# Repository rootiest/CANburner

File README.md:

# CANBurner

This Project originated from the idea of making the swapping process of the Stealthburner front easier.

CANBurner is a PCB design, that works in cooperation with Hartk's 2pc PCB design.

It consists of a front-part and our adapted CANBurner
The CANBurner is the connection PCB between an EBB36 or EBB42 or any CAN module and the movable front PCB.
over the course of the revisions functions were added and the design was changed. 

# Changelog:
## Rev 1.0 (initial design; tested) 19.10.2022

- adapted the footprint of Hartk's Backplate to fit for our purpose
- JST-XH connectors for 2x fans (Hotend and Part-cooling) and 1x LED added
- 2x3 angled pin header to connect to the front PCB 
- simple wire paths over the board
- a through-hole design for easy soldering at home

first tests by André show, that the design fits perfectly on the CW2 extruder. dimensions reach barely past the motor backplate. 
THD components don't collide with each other or the SB. Functions are fully present and the JST connectors make swapping cables easy.
Space can be used more effectively. JST is not as important, the cables can be soldered directly on the Board.

## Rev 2.0 04.11.2022

- Name CANBurner was suggested by rootiest
- added one more JST-XH for I2C connection
- added 2x4 angled pin header 
- placement of connectors were changed
- added Voron Logo 
- minor cleanup of traces and text

## Rev 2L 05.11.2022

- added Neopixel SMD light as status LED
- changed traces
- added voltage test-points for 24V, 5V and GND
- added "rootiest"-Logo

## Rev 3

- fully changed plug design
- one 8 pin JST-PH to connect to CAN board
- 4 pin socket header to allow for direct I2C connection
- SMD LED and solder traces to skip LED when its ot used

## Credits

CANBurner is a collaboration between [Chris Laprade](https://github.com/rootiest/) and [André Bernbrich](https://github.com/Peviox)

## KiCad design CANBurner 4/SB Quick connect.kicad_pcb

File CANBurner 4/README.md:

<!--
 Copyright (C) 2022 Chris Laprade (chris@rootiest.com)
 
 This file is part of CANburner.
 
 CANburner is free software: you can redistribute it and/or modify
 it under the terms of the GNU General Public License as published by
 the Free Software Foundation, either version 3 of the License, or
 (at your option) any later version.
 
 CANburner is distributed in the hope that it will be useful,
 but WITHOUT ANY WARRANTY; without even the implied warranty of
 MERCHANTABILITY or FITNESS FOR A PARTICULAR PURPOSE.  See the
 GNU General Public License for more details.
 
 You should have received a copy of the GNU General Public License
 along with CANburner.  If not, see <http://www.gnu.org/licenses/>.
-->

# CANBurner 3 Beta

## What is it?

CANBurner is an adaptation of hartk's 2-piece StealthBurner PCB.

CANBurner adapts this concept for use on printers with a CANbus toolhead like the BigTreeTech EBB or the Mellow FLY-SHT.

## What is new in the v3 Beta?

Version 3 introduces a new single-connector interface to the toolboard. There is also a solder-bridge for bypassing the onboard LED and a header for directly-attaching i2c devices.

## How does it work?

Just like [hartk's boards](https://github.com/hartk1213/MISC/tree/main/PCBs/Stealthburner_Toolhead_PCB) do!

[Watch this video](https://www.youtube.com/watch?v=PCIwZRPYMZ8)

Instead of attaching a ribbon, our board just connects to the corresponding pins on your CANbus toolboard.

Its purpose is to act as a "quick-connect" bridge that allows you to remove the stealthburner without disconnecting and reconnecting several connectors for components like fans and LEDs.

The pins will align and connect when you attach the stealthburner front to the extruder.

## Credits

CANBurner is a collaboration between [Chris Laprade](https://github.com/rootiest/) and [André Bernbrich](https://github.com/Peviox)

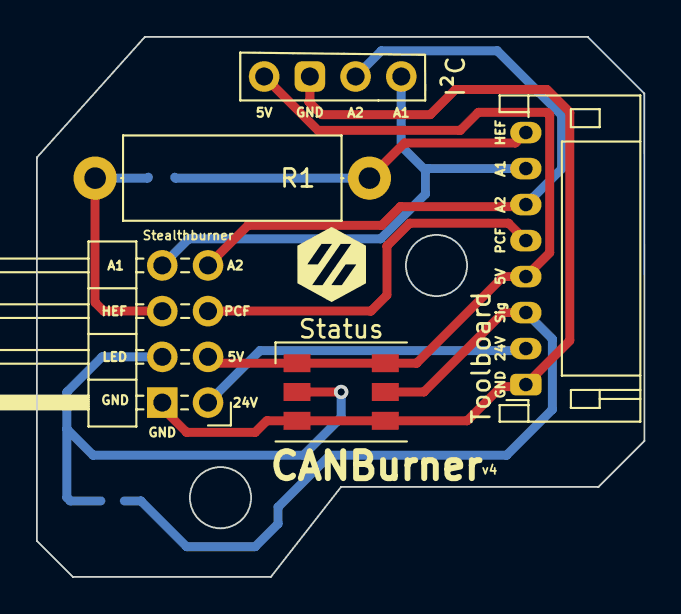
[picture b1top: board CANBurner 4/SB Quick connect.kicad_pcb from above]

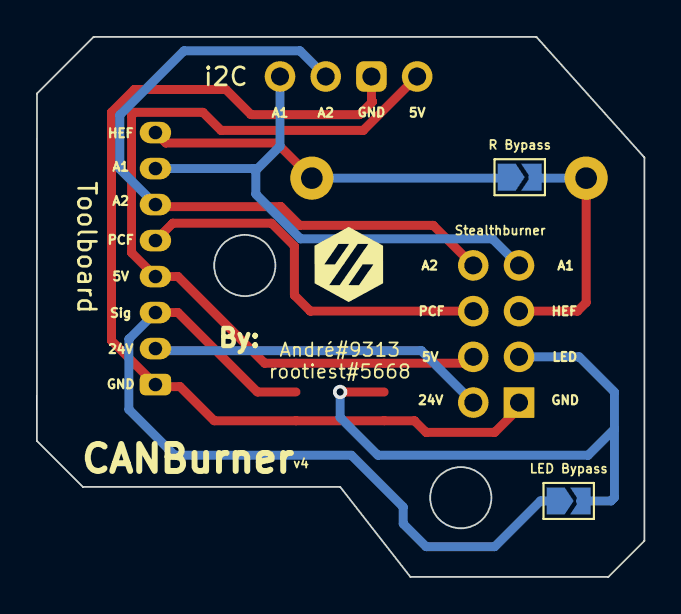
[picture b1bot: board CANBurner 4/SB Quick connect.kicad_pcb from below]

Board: 2 copper layers, 33.8 x 30.0 mm, 7 parts (2 on the bottom side), 8 nets.

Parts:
I²C: i2C Addon; PinSocket_1x04_P2.54mm_Vertical
J1: Conn_02x04_Odd_Even; PinHeader_2x04_P2.54mm_Horizontal
LED Bypass: LED Bypass; SolderJumper-2_P1.3mm_Open_TrianglePad1.0x1.5mm
R1: R; R_Axial_DIN0414_L11.9mm_D4.5mm_P15.24mm_Horizontal
R Bypass: LED Bypass; SolderJumper-2_P1.3mm_Open_TrianglePad1.0x1.5mm
Status: LED_WS2812_PLCC6_5.0x5.0mm_P1.6mm
Toolboard: JST_PH_S8B-PH-K_1x08_P2.00mm_Horizontal

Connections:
/5V: I²C.4, J1.6, Status.1, Status.6, Toolboard.4
/24V: J1.8, Toolboard.2
/A1: I²C.1, J1.1, Toolboard.7
/A2: I²C.2, J1.2, Toolboard.6
/GND: I²C.3, J1.7, Status.3, Status.4, Toolboard.1
/HEF: J1.3, R1.1, R1.2, R Bypass.1, R Bypass.2, Toolboard.8
/PCF: J1.4, Toolboard.5
/Sig: J1.5, LED Bypass.1, LED Bypass.2, Status.2, Status.5, Toolboard.3

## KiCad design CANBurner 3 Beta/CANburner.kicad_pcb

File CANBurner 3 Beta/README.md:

<!--
 Copyright (C) 2022 Chris Laprade (chris@rootiest.com)
 
 This file is part of CANburner.
 
 CANburner is free software: you can redistribute it and/or modify
 it under the terms of the GNU General Public License as published by
 the Free Software Foundation, either version 3 of the License, or
 (at your option) any later version.
 
 CANburner is distributed in the hope that it will be useful,
 but WITHOUT ANY WARRANTY; without even the implied warranty of
 MERCHANTABILITY or FITNESS FOR A PARTICULAR PURPOSE.  See the
 GNU General Public License for more details.
 
 You should have received a copy of the GNU General Public License
 along with CANburner.  If not, see <http://www.gnu.org/licenses/>.
-->

# CANBurner 3 Beta

## What is it?

CANBurner is an adaptation of hartk's 2-piece StealthBurner PCB.

CANBurner adapts this concept for use on printers with a CANbus toolhead like the BigTreeTech EBB or the Mellow FLY-SHT.

## What is new in the v3 Beta?

Version 3 introduces a new single-connector interface to the toolboard. There is also a solder-bridge for bypassing the onboard LED and a header for directly-attaching i2c devices.

## How does it work?

Just like [hartk's boards](https://github.com/hartk1213/MISC/tree/main/PCBs/Stealthburner_Toolhead_PCB) do!

[Watch this video](https://www.youtube.com/watch?v=PCIwZRPYMZ8)

Instead of attaching a ribbon, our board just connects to the corresponding pins on your CANbus toolboard.

Its purpose is to act as a "quick-connect" bridge that allows you to remove the stealthburner without disconnecting and reconnecting several connectors for components like fans and LEDs.

The pins will align and connect when you attach the stealthburner front to the extruder.

## Credits

CANBurner is a collaboration between [Chris Laprade](https://github.com/rootiest/) and [André Bernbrich](https://github.com/Peviox

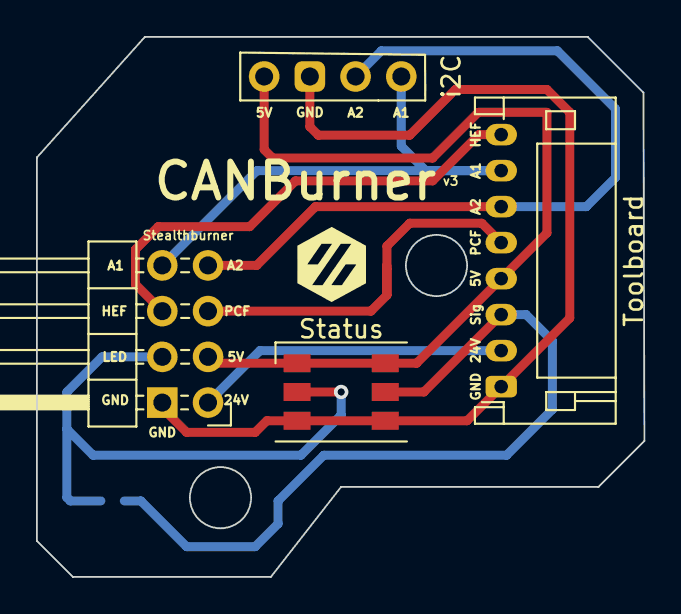
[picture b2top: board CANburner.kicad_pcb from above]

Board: 2 copper layers, 33.8 x 30.0 mm, 5 parts (1 on the bottom side), 8 nets.

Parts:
LED Bypass: LED Bypass; SolderJumper-2_P1.3mm_Open_TrianglePad1.0x1.5mm
Status: LED_WS2812_PLCC6_5.0x5.0mm_P1.6mm
Stealthburner: Conn_02x04_Odd_Even; PinHeader_2x04_P2.54mm_Horizontal
Toolboard: JST_PH_S8B-PH-K_1x08_P2.00mm_Horizontal
i2C: i2C Addon; PinSocket_1x04_P2.54mm_Vertical

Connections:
/5V: Status.1, Status.6, Stealthburner.6, Toolboard.4, i2C.4
/24V: Stealthburner.8, Toolboard.2
/A1: Stealthburner.1, Toolboard.7, i2C.1
/A2: Stealthburner.2, Toolboard.6, i2C.2
/GND: Status.3, Status.4, Stealthburner.7, Toolboard.1, i2C.3
/HEF: Stealthburner.3, Toolboard.8
/PCF: Stealthburner.4, Toolboard.5
/Sig: LED Bypass.1, LED Bypass.2, Status.2, Status.5, Stealthburner.5, Toolboard.3

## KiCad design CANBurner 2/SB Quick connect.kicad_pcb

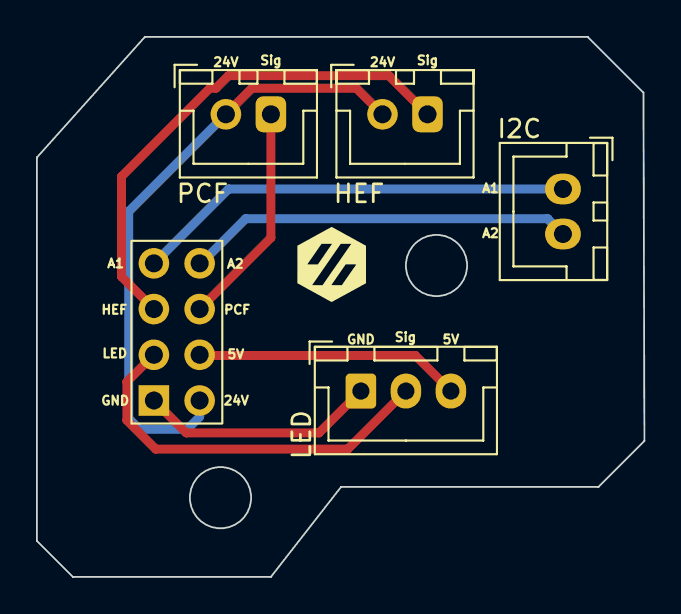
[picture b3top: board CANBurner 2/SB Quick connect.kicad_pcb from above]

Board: 2 copper layers, 33.8 x 30.0 mm, 5 parts (0 on the bottom side), 8 nets.

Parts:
HEF: Conn_01x02; JST_XH_B2B-XH-A_1x02_P2.50mm_Vertical
I2C: Conn_01x02; JST_XH_B2B-XH-A_1x02_P2.50mm_Vertical
J1: Conn_02x04_Odd_Even; PinHeader_2x04_P2.54mm_Vertical
LED: Conn_01x03; JST_XH_B3B-XH-A_1x03_P2.50mm_Vertical
PCF: Conn_01x02; JST_XH_B2B-XH-A_1x02_P2.50mm_Vertical

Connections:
/5V: J1.6, LED.3
/24V: HEF.1, J1.8, PCF.1
/A1: I2C.1, J1.1
/A2: I2C.2, J1.2
/GND: J1.7, LED.1
/HEF: HEF.2, J1.3
/PCF: J1.4, PCF.2
/Sig: J1.5, LED.2

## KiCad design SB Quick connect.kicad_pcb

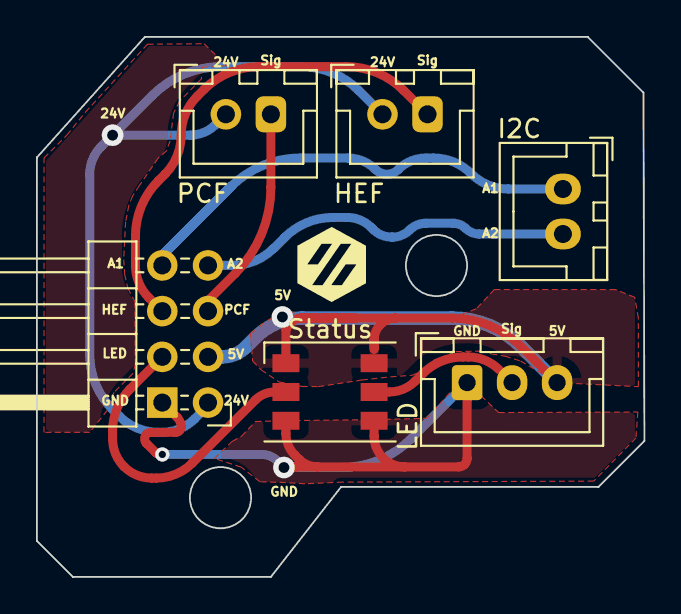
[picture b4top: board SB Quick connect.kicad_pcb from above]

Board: 2 copper layers, 33.8 x 30.0 mm, 6 parts (0 on the bottom side), 8 nets.

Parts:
HEF: Conn_01x02; JST_XH_B2B-XH-A_1x02_P2.50mm_Vertical
I2C: Conn_01x02; JST_XH_B2B-XH-A_1x02_P2.50mm_Vertical
LED: Conn_01x03; JST_XH_B3B-XH-A_1x03_P2.50mm_Vertical
PCF: Conn_01x02; JST_XH_B2B-XH-A_1x02_P2.50mm_Vertical
Status: LED_WS2812_PLCC6_5.0x5.0mm_P1.6mm
Stealthburner: Conn_02x04_Odd_Even; PinHeader_2x04_P2.54mm_Horizontal

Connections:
/5V: LED.3, Status.1, Status.6, Stealthburner.6
/24V: HEF.1, PCF.1, Stealthburner.8
/A1: I2C.1, Stealthburner.1
/A2: I2C.2, Stealthburner.2
/GND: LED.1, Status.3, Status.4, Stealthburner.7
/HEF: HEF.2, Stealthburner.3
/PCF: PCF.2, Stealthburner.4
/Sig: LED.2, Status.2, Status.5, Stealthburner.5

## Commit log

2022-11-05 Create separate folder for version 2L
2022-11-05 Add CANBurner 2 directory
2022-11-05 dictionary
2022-11-05 README
2022-11-06 dictionaries
2022-11-06 formatting
2022-11-06 CANBurner 3 Beta
2022-11-06 Modified pin order on i2c header
    Now fits better with the order most breakouts use.
2022-11-06 Assembly Blueprints
2022-11-06 Minor adjustments to LED Signal tracks
    Moved tracks further from edges/mounting screws
2022-11-06 Another LED Signal Track tweak
    Slightly adjusted the tracks on the bypass pad
    so the path is more obvious when looking at tracks on printed board
2022-11-06 v3 Fixes 🪲⚡
    Added missing track for A1.
    Moved PCF track further from mounting hole.
    Used correct footprint for LED bypass.
2022-11-06 Spelling and MD formatting corrections
2022-11-06 Added Credits section for test
2022-11-06 test
2022-11-06 end test
2022-11-06 Rename KiCAD project files to CANburner
2022-11-12 add fanpcb from hartk
2022-11-12 Rev 4 and fanpcb
2022-11-12 rev 4 changes
2022-11-17 testing
2022-11-17 Fixed Net Trace on resistor for v4
2022-11-18 Fixed solder mask logos over traces
2022-11-20 CANBurner v4 Fabricated
2022-11-20 CANBurner v5
2022-11-20 Update v5 Readme
2023-01-11 CANBurner v5 updates
2023-06-15 add workflows
